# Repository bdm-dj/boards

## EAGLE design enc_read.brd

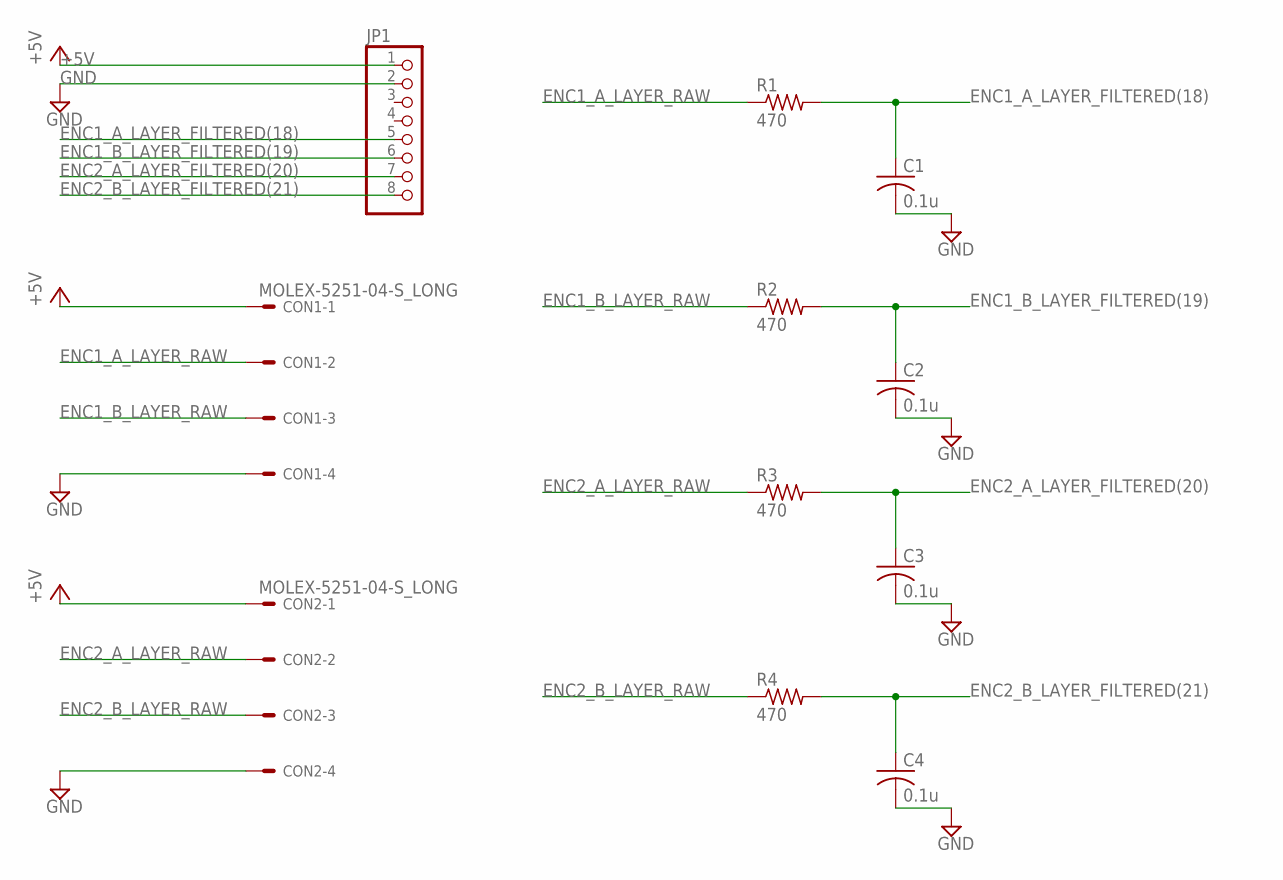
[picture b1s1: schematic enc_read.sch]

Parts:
C1, C2, C3, C4: 0.1u; 2012-C
CON1, CON2: MOLEX-5251-04-S_LONG; 5251-04-S_LONG
JP1: PINHD-1X8; 1X08
R1, R2, R3, R4: 470; 2012-R

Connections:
+5V: CON1.1, CON2.1, JP1.1
ENC1_A_LAYER_FILTERED(18): C1.1, JP1.5, R1.2
ENC1_A_LAYER_RAW: CON1.2, R1.1
ENC1_B_LAYER_FILTERED(19): C2.1, JP1.6, R2.2
ENC1_B_LAYER_RAW: CON1.3, R2.1
ENC2_A_LAYER_FILTERED(20): C3.1, JP1.7, R3.2
ENC2_A_LAYER_RAW: CON2.2, R3.1
ENC2_B_LAYER_FILTERED(21): C4.1, JP1.8, R4.2
ENC2_B_LAYER_RAW: CON2.3, R4.1
GND: C1.2, C2.2, C3.2, C4.2, CON1.4, CON2.4, JP1.2

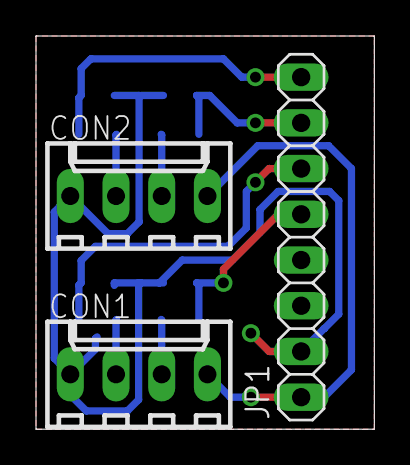
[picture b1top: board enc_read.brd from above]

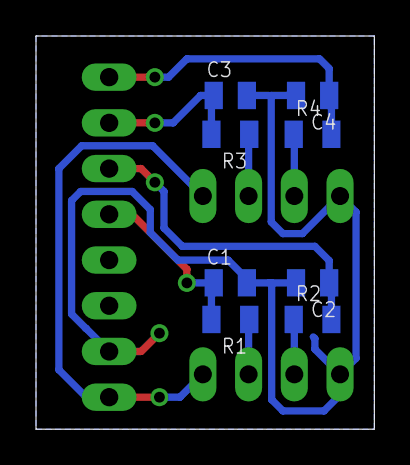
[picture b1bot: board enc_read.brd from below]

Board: 2 copper layers, 18.8 x 21.8 mm, 11 parts (8 on the bottom side), 10 nets.

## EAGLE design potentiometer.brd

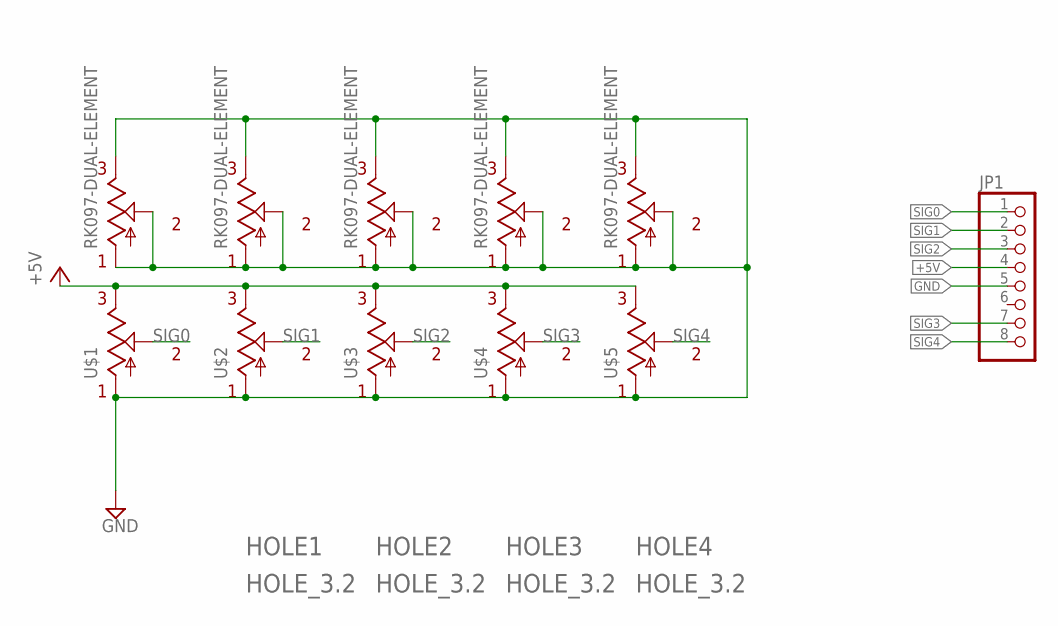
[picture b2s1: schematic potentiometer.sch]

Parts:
HOLE1, HOLE2, HOLE3, HOLE4: HOLE_3.2
JP1: PINHD-1X8; 1X08
U$1, U$2, U$3, U$4, U$5: RK097-DUAL-ELEMENT

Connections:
+5V: JP1.4, U$1.P$4 (E1), U$2.P$4 (E1), U$3.P$4 (E1), U$4.P$4 (E1), U$5.P$4 (E1)
GND: JP1.5, U$1.P$1 (A), U$1.P$2 (A1), U$1.P$3 (E), U$1.P$5 (S), U$2.P$1 (A), U$2.P$2 (A1), U$2.P$3 (E), U$2.P$5 (S), U$3.P$1 (A), U$3.P$2 (A1), U$3.P$3 (E), U$3.P$5 (S), U$4.P$1 (A), U$4.P$2 (A1), U$4.P$3 (E), U$4.P$5 (S), U$5.P$1 (A), U$5.P$2 (A1), U$5.P$3 (E), U$5.P$5 (S)
SIG0: JP1.1, U$1.P$6 (S1)
SIG1: JP1.2, U$2.P$6 (S1)
SIG2: JP1.3, U$3.P$6 (S1)
SIG3: JP1.7, U$4.P$6 (S1)
SIG4: JP1.8, U$5.P$6 (S1)

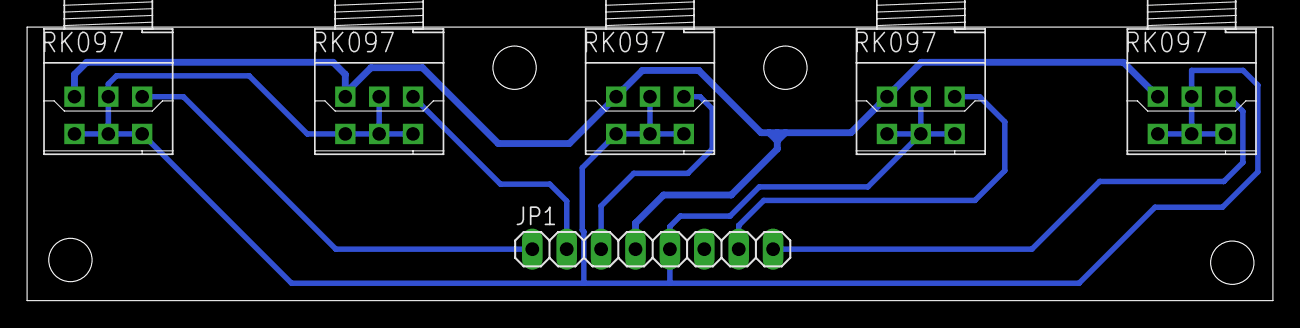
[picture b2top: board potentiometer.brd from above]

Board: 2 copper layers, 92.0 x 20.2 mm, 10 parts (0 on the bottom side), 7 nets.

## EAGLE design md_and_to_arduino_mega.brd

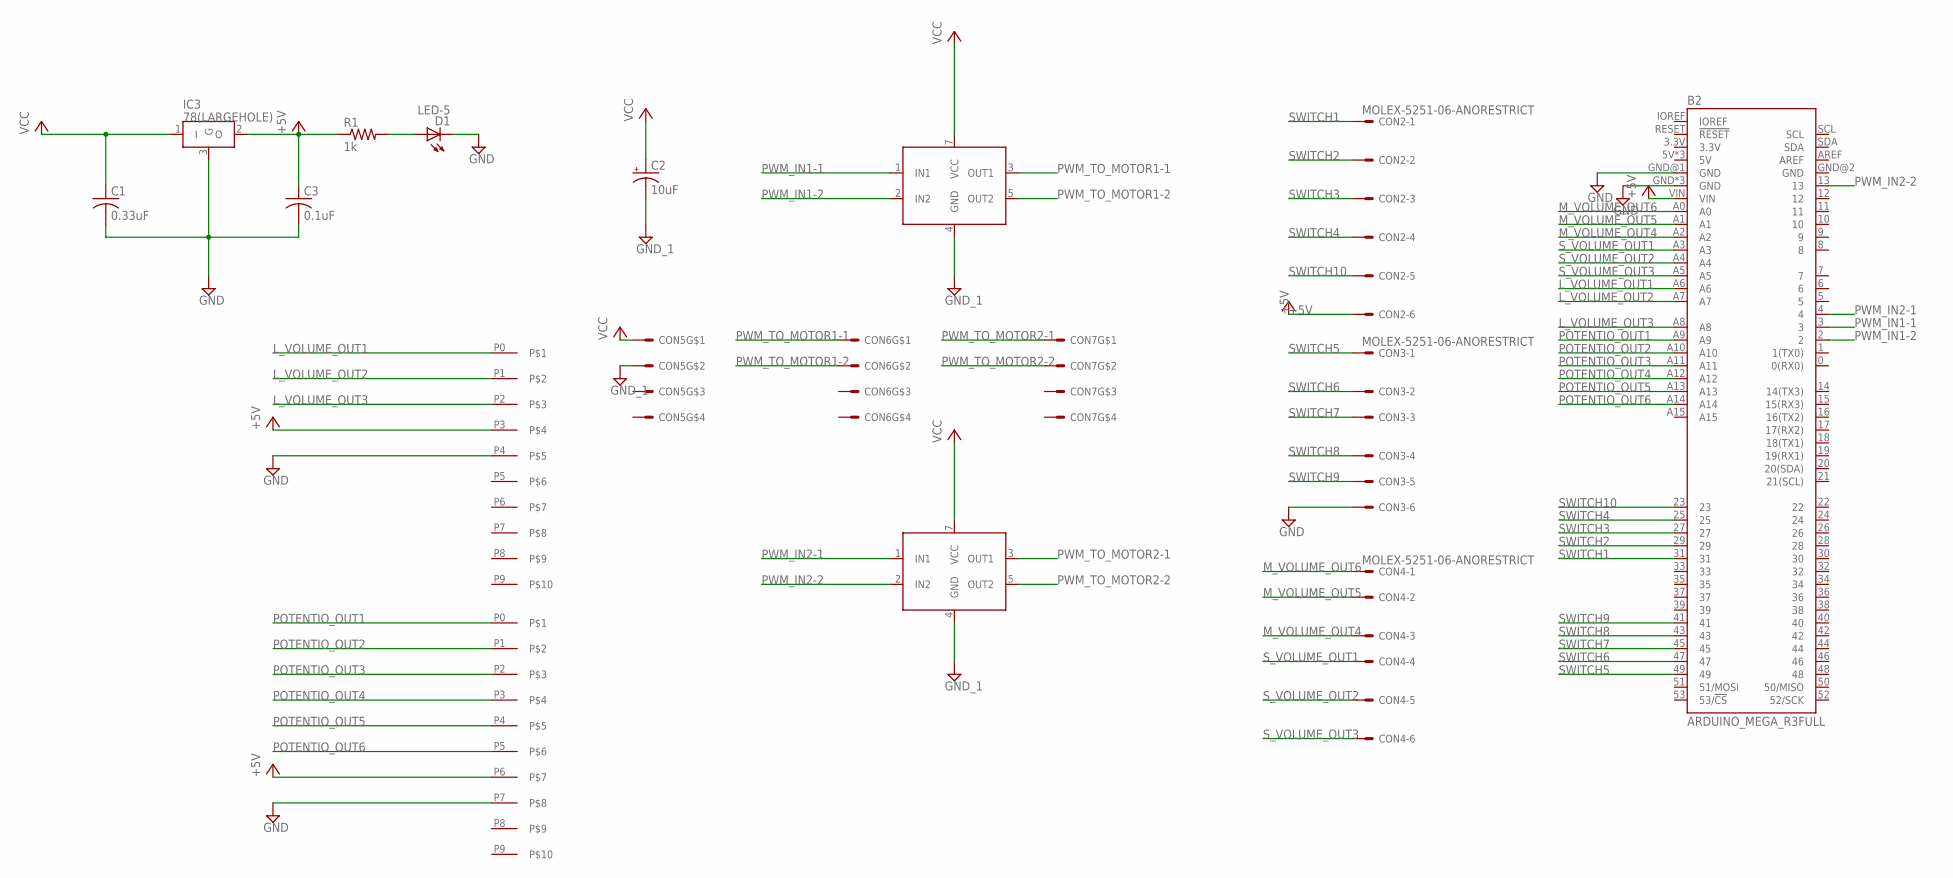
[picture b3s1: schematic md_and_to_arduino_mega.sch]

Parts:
B2: ARDUINO_MEGA_R3FULL; ARDUINO_MEGA_NO_SILK
C1: 0.33uF; 2012-C
C2: 10uF; E5-10,5
C3: 0.1uF; 2012-C
CON2, CON3, CON4: MOLEX-5251-06-ANORESTRICT; 5251-06-ANORESTRICT
CON5, CON6, CON7: D-3200-2-VER2D3200S-2-TAB-VERTICAL-VER2; D3200S-2-TAB-VERTICAL-VER2
D1: LED-5; LED5
IC1, IC2: TA8428K
IC3: 78(LARGEHOLE); 7805-LARGEHOLE
KYABE1, KYABE2: PINSOCKET_1X10
R1: 1k; 2012-R

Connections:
+5V: B2.VIN, C3.1, CON2.6, IC3.2 (O), KYABE1.P6, KYABE2.P3, R1.1
GND: B2.GND, B2.GND@1 (GND), B2.GND@3 (GND), B2.GND@4 (GND), C1.2, C3.2, CON3.6, D1.K, IC3.3 (G), KYABE1.P7, KYABE2.P4
GND_1: C2.-, CON5.2, IC1.4 (GND), IC2.4 (GND)
L_VOLUME_OUT1: B2.A6, KYABE2.P0
L_VOLUME_OUT2: B2.A7, KYABE2.P1
L_VOLUME_OUT3: B2.A8, KYABE2.P2
M_VOLUME_OUT4: B2.A2, CON4.3
M_VOLUME_OUT5: B2.A1, CON4.2
M_VOLUME_OUT6: B2.A0, CON4.1
unnamed: D1.A, R1.2
POTENTIO_OUT1: B2.A9, KYABE1.P0
POTENTIO_OUT2: B2.A10, KYABE1.P1
POTENTIO_OUT3: B2.A11, KYABE1.P2
POTENTIO_OUT4: B2.A12, KYABE1.P3
POTENTIO_OUT5: B2.A13, KYABE1.P4
POTENTIO_OUT6: B2.A14, KYABE1.P5
PWM_IN1-1: B2.3, IC1.1 (IN1)
PWM_IN1-2: B2.2, IC1.2 (IN2)
PWM_IN2-1: B2.4, IC2.1 (IN1)
PWM_IN2-2: B2.13, IC2.2 (IN2)
PWM_TO_MOTOR1-1: CON6.1, IC1.3 (OUT1)
PWM_TO_MOTOR1-2: CON6.2, IC1.5 (OUT2)
PWM_TO_MOTOR2-1: CON7.1, IC2.3 (OUT1)
PWM_TO_MOTOR2-2: CON7.2, IC2.5 (OUT2)
SWITCH1: B2.31, CON2.1
SWITCH2: B2.29, CON2.2
SWITCH3: B2.27, CON2.3
SWITCH4: B2.25, CON2.4
SWITCH5: B2.49, CON3.1
SWITCH6: B2.47, CON3.2
SWITCH7: B2.45, CON3.3
SWITCH8: B2.43, CON3.4
SWITCH9: B2.41, CON3.5
SWITCH10: B2.23, CON2.5
S_VOLUME_OUT1: B2.A3, CON4.4
S_VOLUME_OUT2: B2.A4, CON4.5
S_VOLUME_OUT3: B2.A5, CON4.6
VCC: C1.1, C2.+, CON5.1, IC1.7 (VCC), IC2.7 (VCC), IC3.1 (I)

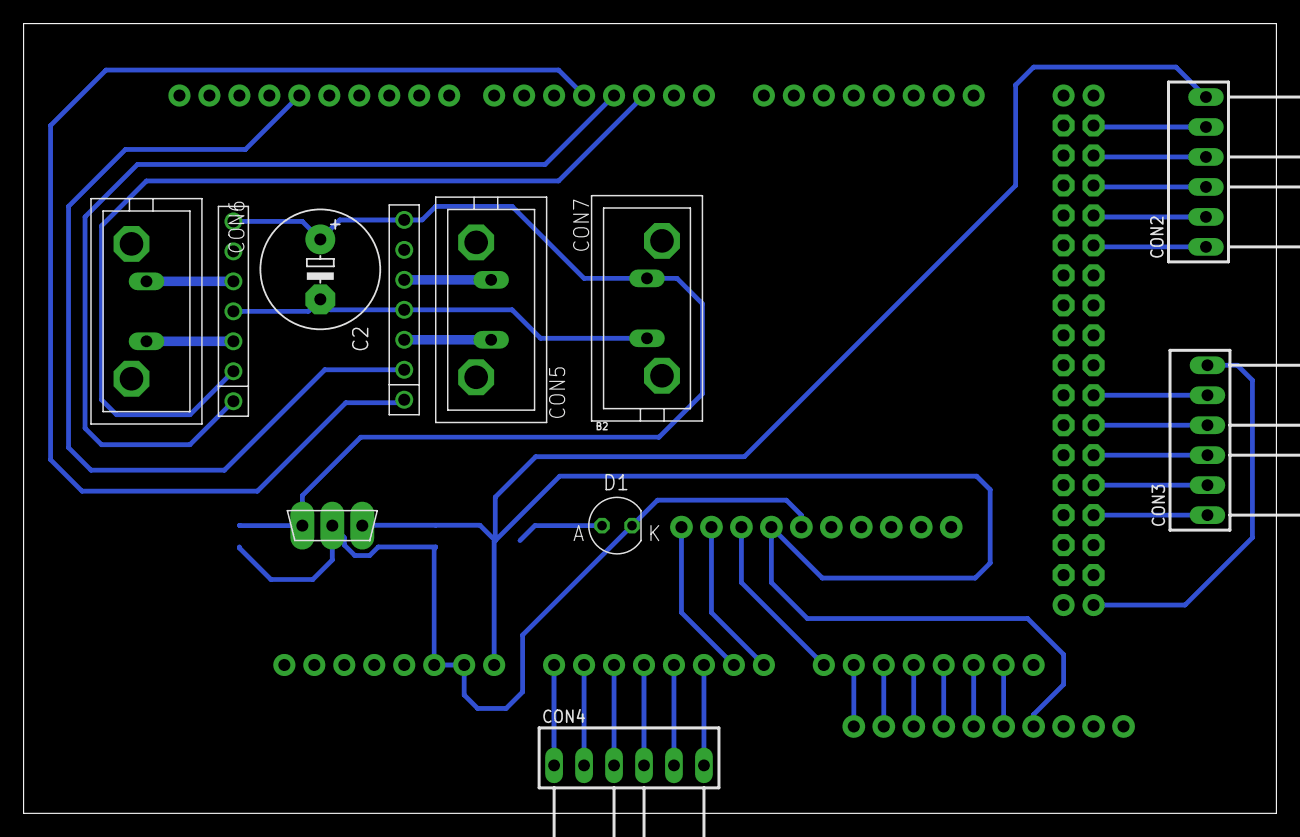
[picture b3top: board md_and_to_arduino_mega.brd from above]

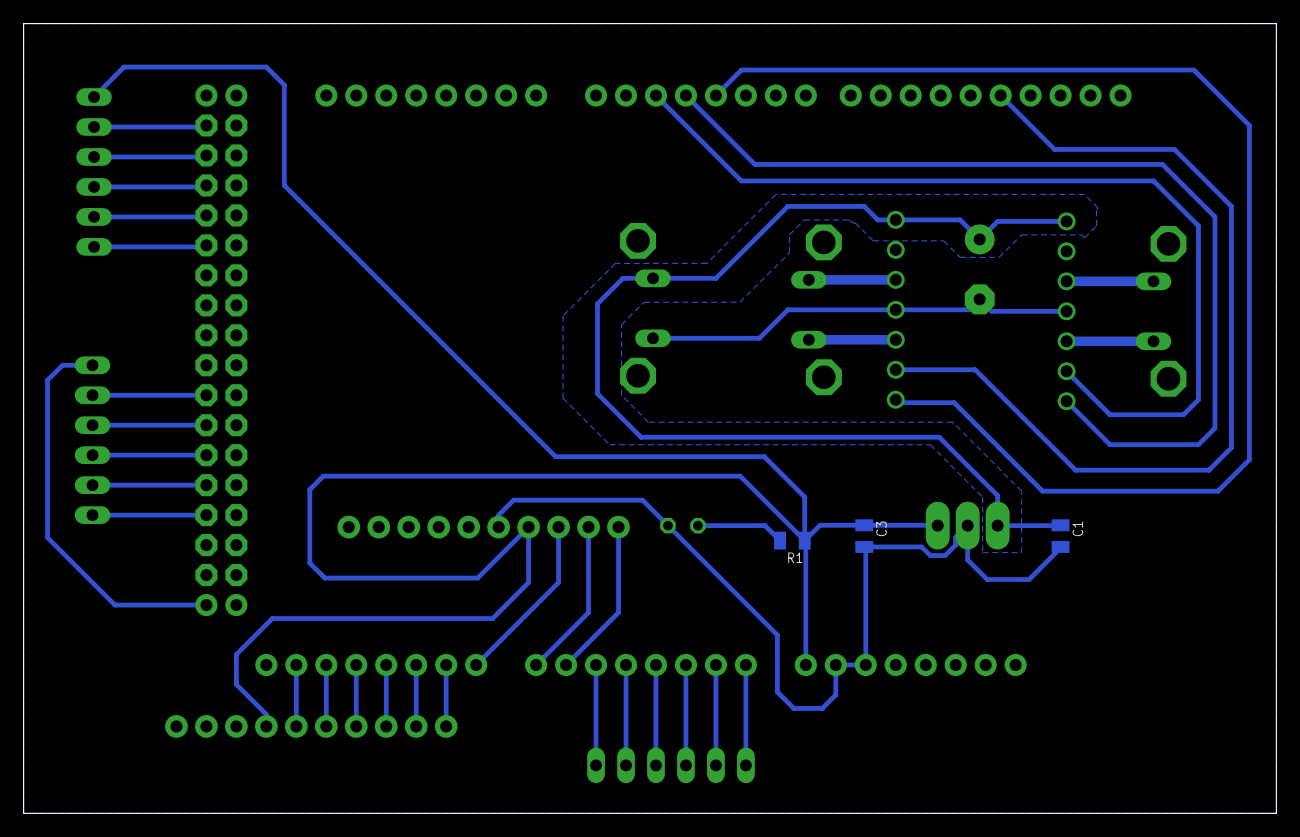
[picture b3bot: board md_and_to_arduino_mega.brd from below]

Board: 2 copper layers, 106.2 x 66.9 mm, 17 parts (3 on the bottom side), 38 nets.

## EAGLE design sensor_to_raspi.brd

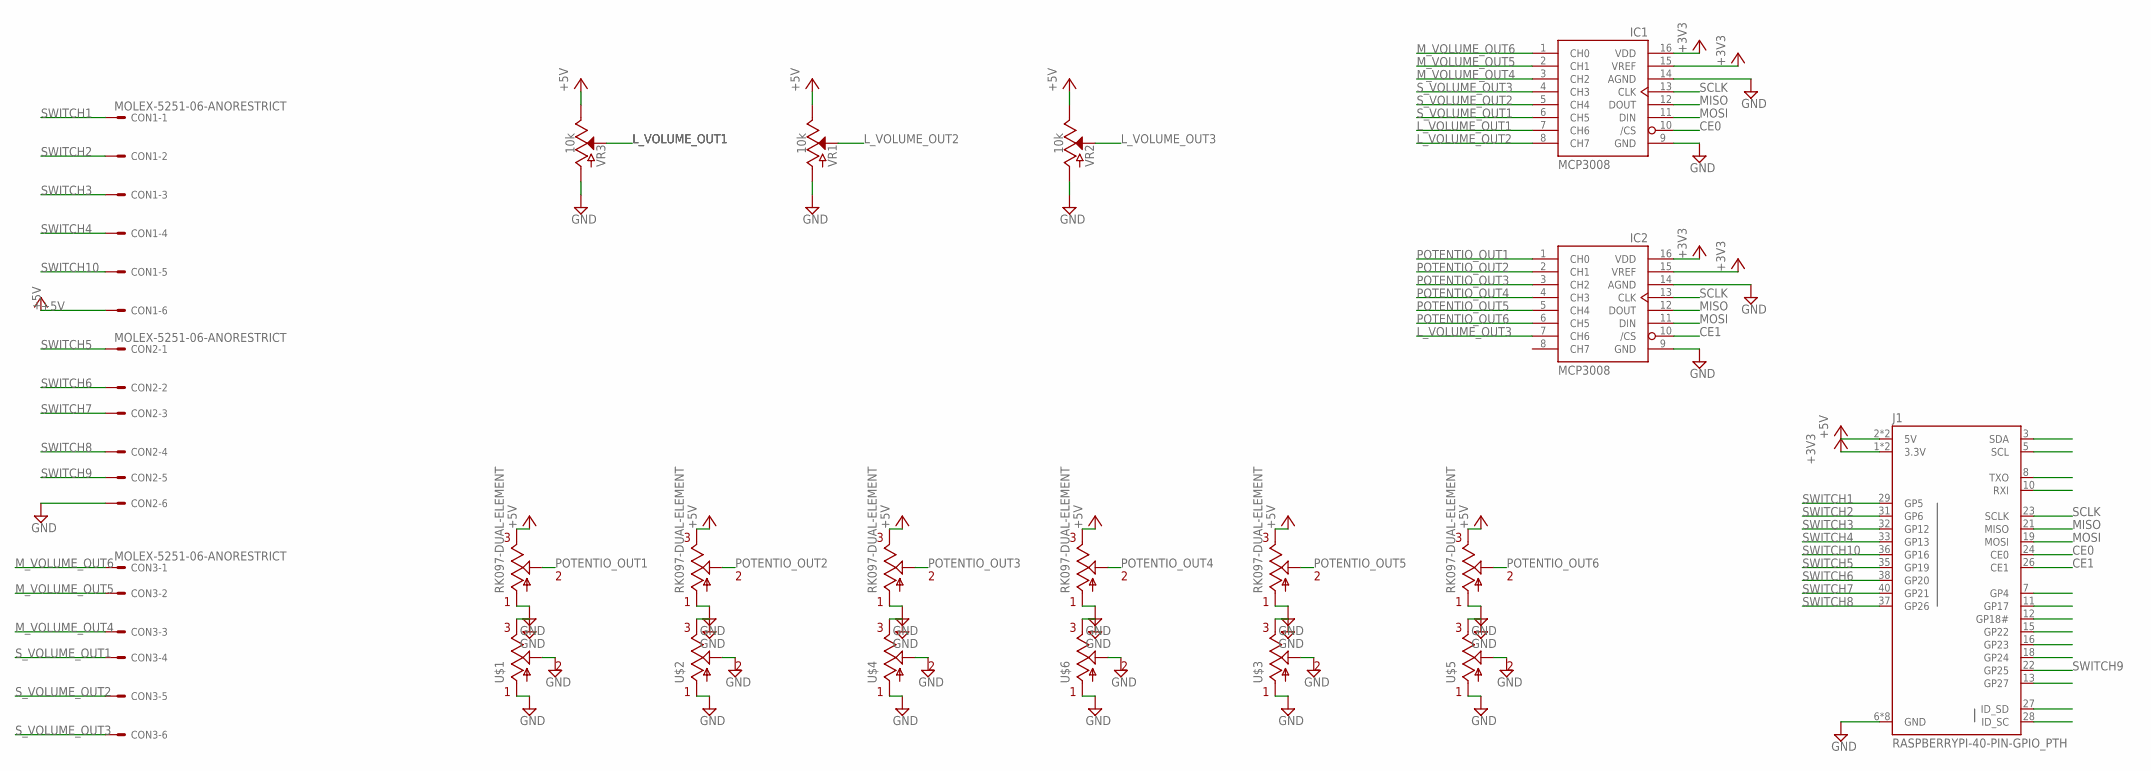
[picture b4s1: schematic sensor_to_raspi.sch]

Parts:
CON1, CON2, CON3: MOLEX-5251-06-ANORESTRICT; 5251-06-ANORESTRICT
IC1, IC2: MCP3008; DIL16
J1: RASPBERRYPI-40-PIN-GPIO_PTH; 2X20_SHROUDED
U$1, U$2, U$3, U$4, U$5, U$6: RK097-DUAL-ELEMENT
VR1, VR2, VR3: 10k; SLIDER-XLARGE

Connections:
+3V3: IC1.15 (VREF), IC1.16 (VDD), IC2.15 (VREF), IC2.16 (VDD), J1.1 (3.3V), J1.17 (3.3V)
+5V: CON1.6, J1.2 (5V), J1.4 (5V), U$1.P$3 (E), U$2.P$3 (E), U$3.P$3 (E), U$4.P$3 (E), U$5.P$3 (E), U$6.P$3 (E), VR1.1 (E), VR2.1 (E), VR3.1 (E)
CE0: IC1.10 (/CS), J1.24 (CE0)
CE1: IC2.10 (/CS), J1.26 (CE1)
GND: CON2.6, IC1.9 (GND), IC1.14 (AGND), IC2.9 (GND), IC2.14 (AGND), J1.6 (GND), J1.9 (GND), J1.14 (GND), J1.20 (GND), J1.25 (GND), J1.30 (GND), J1.34 (GND), J1.39 (GND), U$1.P$1 (A), U$1.P$2 (A1), U$1.P$4 (E1), U$1.P$6 (S1), U$2.P$1 (A), U$2.P$2 (A1), U$2.P$4 (E1), U$2.P$6 (S1), U$3.P$1 (A), U$3.P$2 (A1), U$3.P$4 (E1), U$3.P$6 (S1), U$4.P$1 (A), U$4.P$2 (A1), U$4.P$4 (E1), U$4.P$6 (S1), U$5.P$1 (A), U$5.P$2 (A1), U$5.P$4 (E1), U$5.P$6 (S1), U$6.P$1 (A), U$6.P$2 (A1), U$6.P$4 (E1), U$6.P$6 (S1), VR1.3 (A), VR2.3 (A), VR3.3 (A)
L_VOLUME_OUT1: IC1.7 (CH6), VR3.2A (S)
L_VOLUME_OUT2: IC1.8 (CH7), VR1.2A (S)
L_VOLUME_OUT3: IC2.7 (CH6), VR2.2A (S)
MISO: IC1.12 (DOUT), IC2.12 (DOUT), J1.21 (MISO)
MOSI: IC1.11 (DIN), IC2.11 (DIN), J1.19 (MOSI)
M_VOLUME_OUT4: CON3.3, IC1.3 (CH2)
M_VOLUME_OUT5: CON3.2, IC1.2 (CH1)
M_VOLUME_OUT6: CON3.1, IC1.1 (CH0)
POTENTIO_OUT1: IC2.1 (CH0), U$1.P$5 (S)
POTENTIO_OUT2: IC2.2 (CH1), U$2.P$5 (S)
POTENTIO_OUT3: IC2.3 (CH2), U$4.P$5 (S)
POTENTIO_OUT4: IC2.4 (CH3), U$6.P$5 (S)
POTENTIO_OUT5: IC2.5 (CH4), U$3.P$5 (S)
POTENTIO_OUT6: IC2.6 (CH5), U$5.P$5 (S)
SCLK: IC1.13 (CLK), IC2.13 (CLK), J1.23 (SCLK)
SWITCH1: CON1.1, J1.29 (GP5)
SWITCH2: CON1.2, J1.31 (GP6)
SWITCH3: CON1.3, J1.32 (GP12)
SWITCH4: CON1.4, J1.33 (GP13)
SWITCH5: CON2.1, J1.35 (GP19)
SWITCH6: CON2.2, J1.38 (GP20)
SWITCH7: CON2.3, J1.40 (GP21)
SWITCH8: CON2.4, J1.37 (GP26)
SWITCH9: CON2.5, J1.22 (GP25)
SWITCH10: CON1.5, J1.36 (GP16)
S_VOLUME_OUT1: CON3.4, IC1.6 (CH5)
S_VOLUME_OUT2: CON3.5, IC1.5 (CH4)
S_VOLUME_OUT3: CON3.6, IC1.4 (CH3)

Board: 2 copper layers, 17 parts (0 on the bottom side), 33 nets, no tracks yet.

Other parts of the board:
D1: LED-3; LED3
R1: 2012-R

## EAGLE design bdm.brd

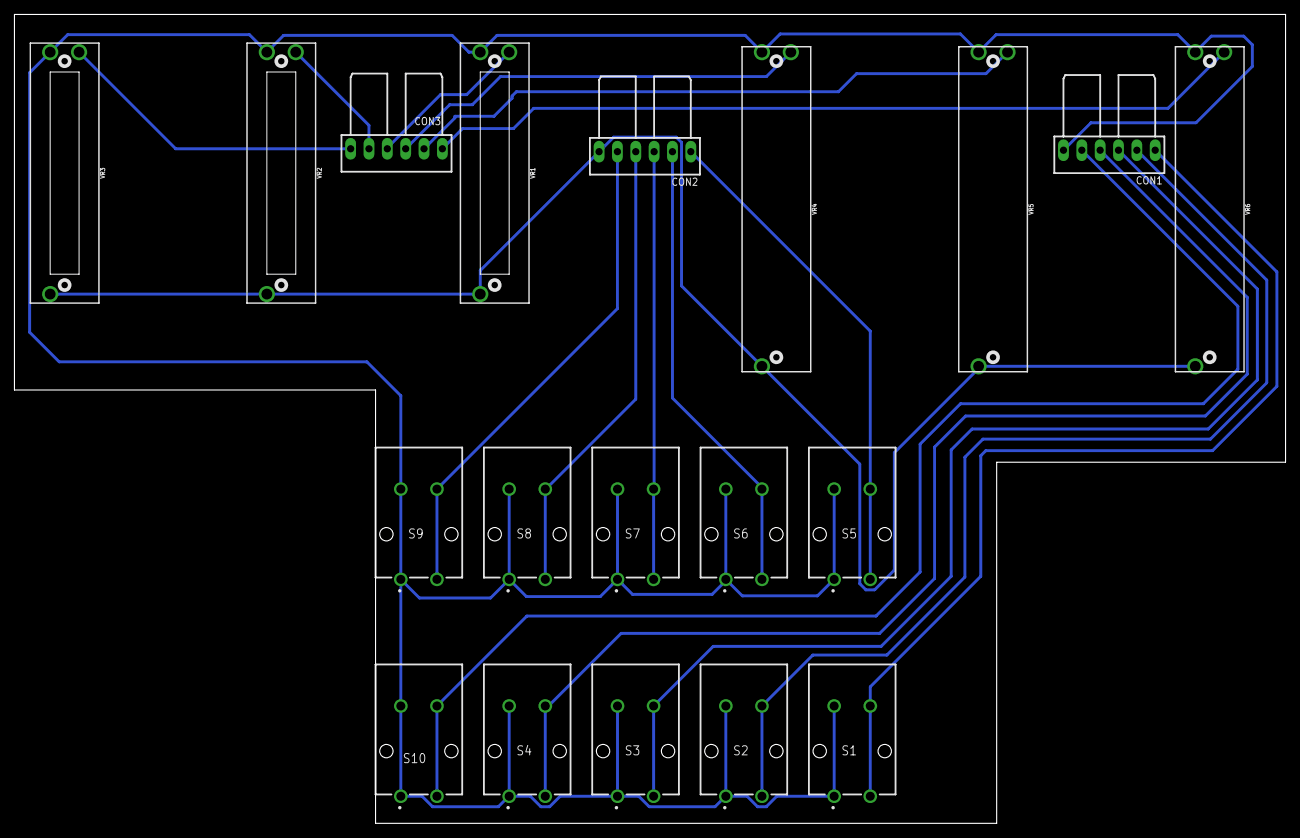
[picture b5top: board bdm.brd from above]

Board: 2 copper layers, 176.0 x 112.0 mm, 19 parts (0 on the bottom side), 18 nets.

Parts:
CON1, CON2, CON3: MOLEX-5251-06-ANORESTRICT; 5251-06-ANORESTRICT
S1, S2, S3, S4, S5, S6, S7, S8, S9, S10: B3J-1000; B3J-1_00
VR1, VR2, VR3: 10k; SLIDER-SMALL
VR4, VR5, VR6: 10k; SLIDER-MEDIUM

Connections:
+5V: CON1.6, S1.1, S1.2, S2.1, S2.2, S3.1, S3.2, S4.1, S4.2, S5.1, S5.2, S6.1, S6.2, S7.1, S7.2, S8.1, S8.2, S9.1, S9.2, S10.1, S10.2, VR1.TOP, VR2.TOP, VR3.TOP, VR4.TOP, VR5.TOP, VR6.TOP
GND: CON2.6, VR1.BOTTOM, VR2.BOTTOM, VR3.BOTTOM, VR4.BOTTOM, VR5.BOTTOM, VR6.BOTTOM
OUT1: CON1.1, S1.3, S1.4
OUT2: CON1.2, S2.3, S2.4
OUT3: CON1.3, S3.3, S3.4
OUT4: CON1.4, S4.3, S4.4
OUT5: CON2.1, S5.3, S5.4
OUT6: CON2.2, S6.3, S6.4
OUT7: CON2.3, S7.3, S7.4
OUT8: CON2.4, S8.3, S8.4
OUT9: CON2.5, S9.3, S9.4
OUT10: CON1.5, S10.3, S10.4
VOLUME_OUT1: CON3.4, VR1.WIPER
VOLUME_OUT2: CON3.5, VR2.WIPER
VOLUME_OUT3: CON3.6, VR3.WIPER
VOLUME_OUT4: CON3.3, VR4.WIPER
VOLUME_OUT5: CON3.2, VR5.WIPER
VOLUME_OUT6: CON3.1, VR6.WIPER

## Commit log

2019-12-27 first brd and sch
2019-12-30 first Board completed
2019-12-30 edit the position of volumes
2019-12-30 changed the size
2019-12-30 second changed the size
2019-12-30 add the hole
2019-12-30 fuck you
2020-01-02 ひとまず回路図だけ書いてみた。check求む
2020-01-06 刷った基盤ンゴ
2020-01-06 timer3を用いた片方のモーターをまわすarduinoコード
2020-01-08 エンコーダーを読む基盤
2020-01-08 refine enc_read.brd
2020-01-08 add potentiometer fucking board
2020-01-09 両面基板にした

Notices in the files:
parts and their libraries:
SparkFun-Resistors: Licensing: Creative Commons ShareAlike 4.0 International - https://creativecommons.org/licenses/by-sa/4.0
